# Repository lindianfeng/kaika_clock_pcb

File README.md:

# kaika_clock_pcb
kaika_clock_pcb

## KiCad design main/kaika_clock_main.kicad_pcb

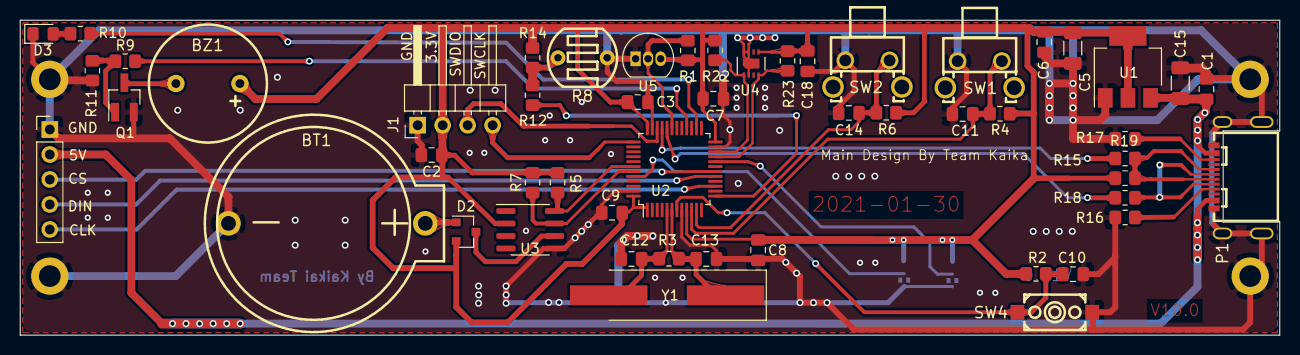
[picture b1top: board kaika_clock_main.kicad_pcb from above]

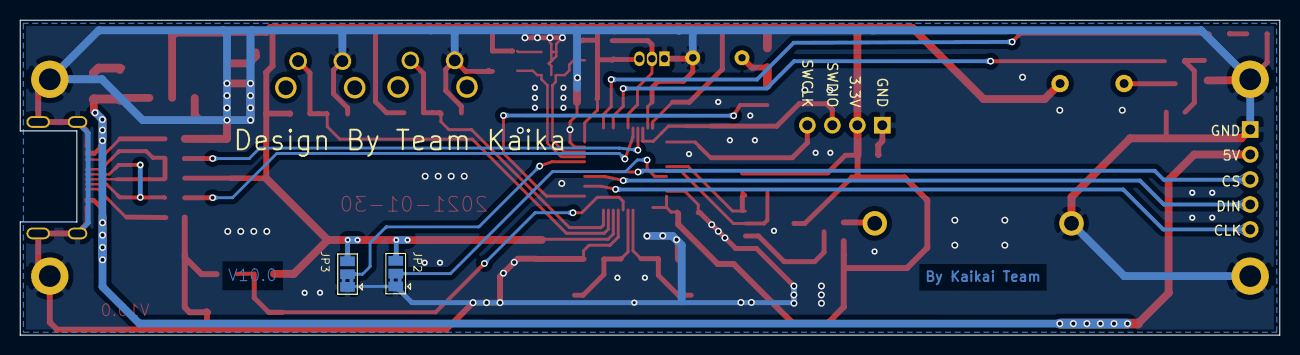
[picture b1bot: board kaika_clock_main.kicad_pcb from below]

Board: 2 copper layers, 128.0 x 32.0 mm, 58 parts (2 on the bottom side), 35 nets.

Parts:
BT1: Battery_Cell; BAT-TH_BS-2-1
BZ1: Buzzer; BUZZER-TH_BD12.0-P6.50-D0.6-FD
C1, C2, C3, C6, C7, C8, C9, C10, C11, C14, C18: 100nf; C_0805_2012Metric_Pad1.18x1.45mm_HandSolder
C5, C15: 47uf; C_1206_3216Metric_Pad1.33x1.80mm_HandSolder
C12, C13: 20p; C_0805_2012Metric_Pad1.18x1.45mm_HandSolder
D2: BAT54C; SOT-23
D3: D1; LED_0805_2012Metric_Pad1.15x1.40mm_HandSolder
H1, H2, H3, H4: MountingHole; MountingHole_2.2mm_M2_DIN965_Pad
J1: Conn_01x04; PinHeader_1x04_P2.54mm_Horizontal
J2: Conn_01x05; PinHeader_1x05_P2.54mm_Vertical
JP2, JP3: Jumper_NC_Dual; SolderJumper-3_P1.3mm_Bridged2Bar12_Pad1.0x1.5mm
P1: USB-C-SMD_TYPE-C16PIN_C168688; USB-C-SMD_TYPE-C-USB-4_C168688
Q1: Q_NPN_BEC; SOT-23_Handsoldering
R1, R16, R17: 5.1K; R_0805_2012Metric_Pad1.20x1.40mm_HandSolder
R2, R4, R6, R9: 10K; R_0805_2012Metric_Pad1.20x1.40mm_HandSolder
R3: 1M; R_0805_2012Metric_Pad1.20x1.40mm_HandSolder
R5, R7, R22, R23: 4.7K; R_0805_2012Metric_Pad1.20x1.40mm_HandSolder
R8: RES-GL7516; RES-TH_L7.0-W5.9-P5.00-D0.5
R10: 200; R_0805_2012Metric_Pad1.20x1.40mm_HandSolder
R11, R12: 1K; R_0805_2012Metric_Pad1.20x1.40mm_HandSolder
R14: 22K; R_0805_2012Metric_Pad1.20x1.40mm_HandSolder
R15: 1.5K; R_0805_2012Metric_Pad1.20x1.40mm_HandSolder
R18, R19: 33; R_0805_2012Metric_Pad1.20x1.40mm_HandSolder
SW1, SW2: TC-1102N-C-QL-B; SW-TH_TC-1102N-C-QL-B
SW4: KEY-SMD_2P-L6.2-W3.6-LS8.0; SW-SMD_L6.2-W3.6-LS8.0
U1: AMS1117-3.3; SOT-223-3_TabPin2
U2: STM32F103C8Tx; LQFP-48_7x7mm_P0.5mm
U3: DS3231MZ; SOIC-8_3.9x4.9mm_P1.27mm
U4: SHT30-DIS; Sensirion_DFN-8-1EP_2.5x2.5mm_P0.5mm_EP1.1x1.7mm
U5: DS18B20; TO-92_Inline
Y1: 8MHZ; Crystal_SMD_HC49-SD_HandSoldering

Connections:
+3V3: BZ1.1, C2.1, C3.1, C5.1, C6.1, C7.1, C8.1, C9.1, C18.1, D2.2, J1.2, JP2.3, JP3.3, R1.2, R2.1, R4.1, R5.2, R6.1, R7.2, R14.2, R15.1, R22.2, R23.2, U1.2, U2.1, U2.9, U2.24, U2.36, U2.48, U3.2, U4.5, U5.3
BEEP: R9.2, U2.28
BOOT0: JP2.2, U2.44
BOOT1: JP3.2, U2.20
D+: P1.A6, P1.B6, R15.2, R19.1
D-: P1.A7, P1.B7, R18.1
DS18B20: R1.1, U2.31, U5.2
GND: BT1.2, C1.2, C2.2, C3.2, C5.2, C6.2, C7.2, C8.2, C9.2, C10.1, C11.1, C12.1, C13.1, C14.1, C15.2, C18.2, D3.1, H1.1, H2.1, H3.1, H4.1, J1.1, J2.1, JP2.1, JP3.1, P1.0, P1.A1, P1.A12, P1.B1, P1.B12, Q1.2, R8.1, R11.1, R16.2, R17.2, SW1.2, SW2.2, SW4.2, U1.1, U2.8, U2.23, U2.35, U2.47, U3.5, U4.2, U4.7, U4.8, U4.9, U5.1
I2C1_SCL: R5.1, U2.42, U3.8
I2C1_SDA: R7.1, U2.43, U3.7
I2C2_SCL: R23.1, U2.21, U4.4
I2C2_SDA: R22.1, U2.22, U4.1
KEY1: C11.2, R4.2, SW1.1, U2.10
KEY2: C14.2, R6.2, SW2.1, U2.11
LIGHT_SENSOR: R12.2, U2.13
unnamed: BT1.1, D2.1
unnamed: BZ1.2, Q1.3
unnamed: D2.3, U3.6
unnamed: D3.2, R10.1
unnamed: P1.A5, R16.1
unnamed: P1.B5, R17.1
unnamed: Q1.1, R9.1, R11.2
unnamed: R8.2, R12.1, R14.1
OSC_IN: C12.2, R3.1, U2.5, Y1.2
OSC_OUT: C13.2, R3.2, U2.6, Y1.1
RESET: C10.2, R2.2, SW4.1, U2.7
RUN_LED: R10.2, U2.26
SPI1_CS: J2.3, U2.18
SPI1_MOSI: J2.4, U2.17
SPI1_SCK: J2.5, U2.15
SWCLK: J1.4, U2.37
SWDIO: J1.3, U2.34
USB_D+: R19.2, U2.33
USB_D-: R18.2, U2.32
VCC: C1.1, C15.1, J2.2, P1.A4, P1.A9, P1.B4, P1.B9, U1.3

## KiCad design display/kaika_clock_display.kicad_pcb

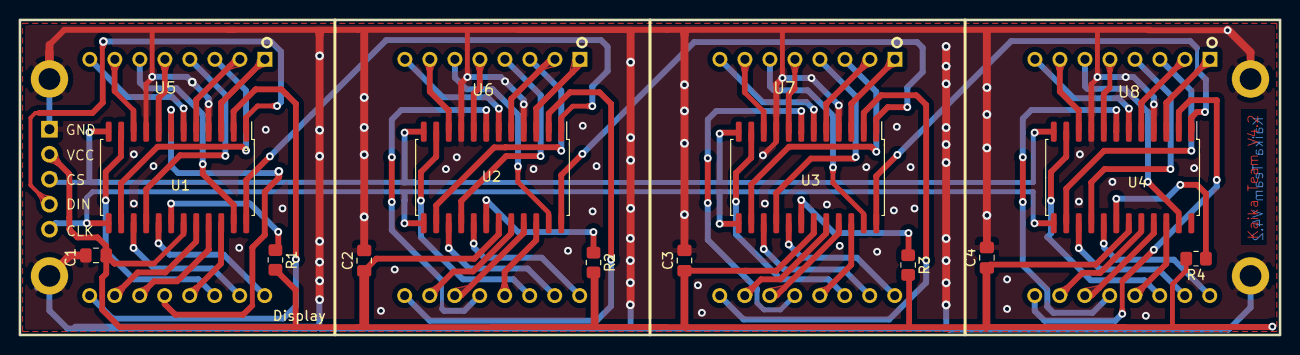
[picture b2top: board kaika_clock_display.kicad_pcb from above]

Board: 2 copper layers, 128.0 x 32.0 mm, 21 parts (1 on the bottom side), 76 nets.

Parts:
C1, C2, C3, C4: 100nf; C_0805_2012Metric_Pad1.18x1.45mm_HandSolder
H1, H2, H3, H4: MountingHole; MountingHole_2.2mm_M2_DIN965_Pad
J1: Conn_01x05; PinHeader_1x05_P2.54mm_Vertical
R1, R2, R3, R4: 10K; R_0805_2012Metric_Pad1.20x1.40mm_HandSolder
U1, U2, U3, U4: MAX7219; SOIC-24W_7.5x15.4mm_P1.27mm
U5, U6, U7, U8: LED-MATRIX-1088AS; LED-DISPLAY-1088AS

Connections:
1_DIG_0: U1.2, U5.9
1_DIG_1: U1.11, U5.14
1_DIG_2: U1.6, U5.8
1_DIG_3: U1.7, U5.12
1_DIG_4: U1.3, U5.1
1_DIG_5: U1.10, U5.7
1_DIG_6: U1.5, U5.2
1_DIG_7: U1.8, U5.5
1_SEG_A: U1.14, U5.3
1_SEG_B: U1.16, U5.4
1_SEG_C: U1.20, U5.10
1_SEG_D: U1.23, U5.6
1_SEG_DP: U1.22, U5.13
1_SEG_E: U1.21, U5.11
1_SEG_F: U1.15, U5.15
1_SEG_G: U1.17, U5.16
2_DIG_0: U2.2, U6.9
2_DIG_1: U2.11, U6.14
2_DIG_2: U2.6, U6.8
2_DIG_3: U2.7, U6.12
2_DIG_4: U2.3, U6.1
2_DIG_5: U2.10, U6.7
2_DIG_6: U2.5, U6.2
2_DIG_7: U2.8, U6.5
2_SEG_A: U2.14, U6.3
2_SEG_B: U2.16, U6.4
2_SEG_C: U2.20, U6.10
2_SEG_D: U2.23, U6.6
2_SEG_DP: U2.22, U6.13
2_SEG_E: U2.21, U6.11
2_SEG_F: U2.15, U6.15
2_SEG_G: U2.17, U6.16
3_DIG_0: U3.2, U7.9
3_DIG_1: U3.11, U7.14
3_DIG_2: U3.6, U7.8
3_DIG_3: U3.7, U7.12
3_DIG_4: U3.3, U7.1
3_DIG_5: U3.10, U7.7
3_DIG_6: U3.5, U7.2
3_DIG_7: U3.8, U7.5
3_SEG_A: U3.14, U7.3
3_SEG_B: U3.16, U7.4
3_SEG_C: U3.20, U7.10
3_SEG_D: U3.23, U7.6
3_SEG_DP: U3.22, U7.13
3_SEG_E: U3.21, U7.11
3_SEG_F: U3.15, U7.15
3_SEG_G: U3.17, U7.16
4_DIG_0: U4.2, U8.9
4_DIG_1: U4.11, U8.14
4_DIG_2: U4.6, U8.8
4_DIG_3: U4.7, U8.12
4_DIG_4: U4.3, U8.1
4_DIG_5: U4.10, U8.7
4_DIG_6: U4.5, U8.2
4_DIG_7: U4.8, U8.5
4_SEG_A: U4.14, U8.3
4_SEG_B: U4.16, U8.4
4_SEG_C: U4.20, U8.10
4_SEG_D: U4.23, U8.6
4_SEG_DP: U4.22, U8.13
4_SEG_E: U4.21, U8.11
4_SEG_F: U4.15, U8.15
4_SEG_G: U4.17, U8.16
CLK: J1.5, U1.13, U2.13, U3.13, U4.13
DIN: J1.4, U1.1
GND: C1.2, C2.2, C3.2, C4.2, H1.1, H2.1, H3.1, H4.1, J1.1, U1.4, U1.9, U2.4, U2.9, U3.4, U3.9, U4.4, U4.9
LOAD: J1.3, U1.12, U2.12, U3.12, U4.12
unnamed: R1.1, U1.18
unnamed: R2.1, U2.18
unnamed: R3.1, U3.18
unnamed: R4.1, U4.18
unnamed: U1.24, U2.1
unnamed: U2.24, U3.1
unnamed: U3.24, U4.1
VCC: C1.1, C2.1, C3.1, C4.1, J1.2, R1.2, R2.2, R3.2, R4.2, U1.19, U2.19, U3.19, U4.19

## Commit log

2020-12-25 add pcb files
2020-12-27 finish the main pcb
2020-12-27 add the display files
2020-12-28 continue work on the display
2020-12-28 modify the main and display
2020-12-28 change usb footprint
2020-12-28 modify the sch
2020-12-28 update the main pcb
2020-12-28 add the gerber files
2020-12-28 finish display board draw.
2020-12-29 finish the project
2020-12-29 modify display vcc to 5v and add the beep
2020-12-29 modify the main
2020-12-30 modify the bat footprints
2020-12-30 modify main pcb
2020-12-31 add the i2l pull up res.
2020-12-31 modify the main pcb
2021-01-01 modify the jumper
2021-01-02 modify change usb to typc-c
2021-01-03 modify main
2021-01-05 modify the display
2021-01-05 modify diplay
2021-01-06 手工布线版本的显示板
2021-01-07 modify main and display
2021-01-10 change dht11 vcc to 3.3v
2021-01-11 modify the main borad
2021-01-15 add 18b20 support
2021-01-19 add at24c128 eeprom support
2021-01-19 change usb footpin
2021-01-21 add sht30 support ,remove dht11. V9.5
2021-01-22 modify the main,v9.6
2021-01-24 i am back,rework the main
2021-01-24 add sht30 support,is the V10.0
2021-01-25 modify the sch,format the sch
2021-01-26 add the ds18b20
